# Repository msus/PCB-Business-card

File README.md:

# PCB Business Card with TicTacToe
#Main Points
- Designed around the Texas Instruments MSP430 series [g2553 16 bit MCU](https://www.ti.com/product/MSP430G2553).
- PCB schematics and board layout files for EAGLE are included.
- The PCB allows to play vs another human OR vs minimax algorithem.

#Image

#MCU LEDs pinout
MCU Pin | LED |MCU Pin | LED |MCU Pin | LED 
:-----:|:----:|:----:|:----:|:----:|:----:
P3.4  |  BLUE 2   |   P3.1  |  BLUE 1  |   P1.0  | BLUE 0
P2.3  |  RED  2   |   P3.0  |  RED  1   |   P1.1  |  RED  0
P2.4  |  BLUE 5   |   P2.0  |  BLUE 4  |   P1.2  |  BLUE 3
P2.5  |  RED  5   |   P2.1  |  RED  4   |   P1.3  |  RED  3
P3.5  |  BLUE 8   |   P2.2  |  BLUE 7  |   P1.4  |  BLUE 6
P3.6  |  RED  8   |   P3.2  |  RED  7   |   P1.5  |  RED  6

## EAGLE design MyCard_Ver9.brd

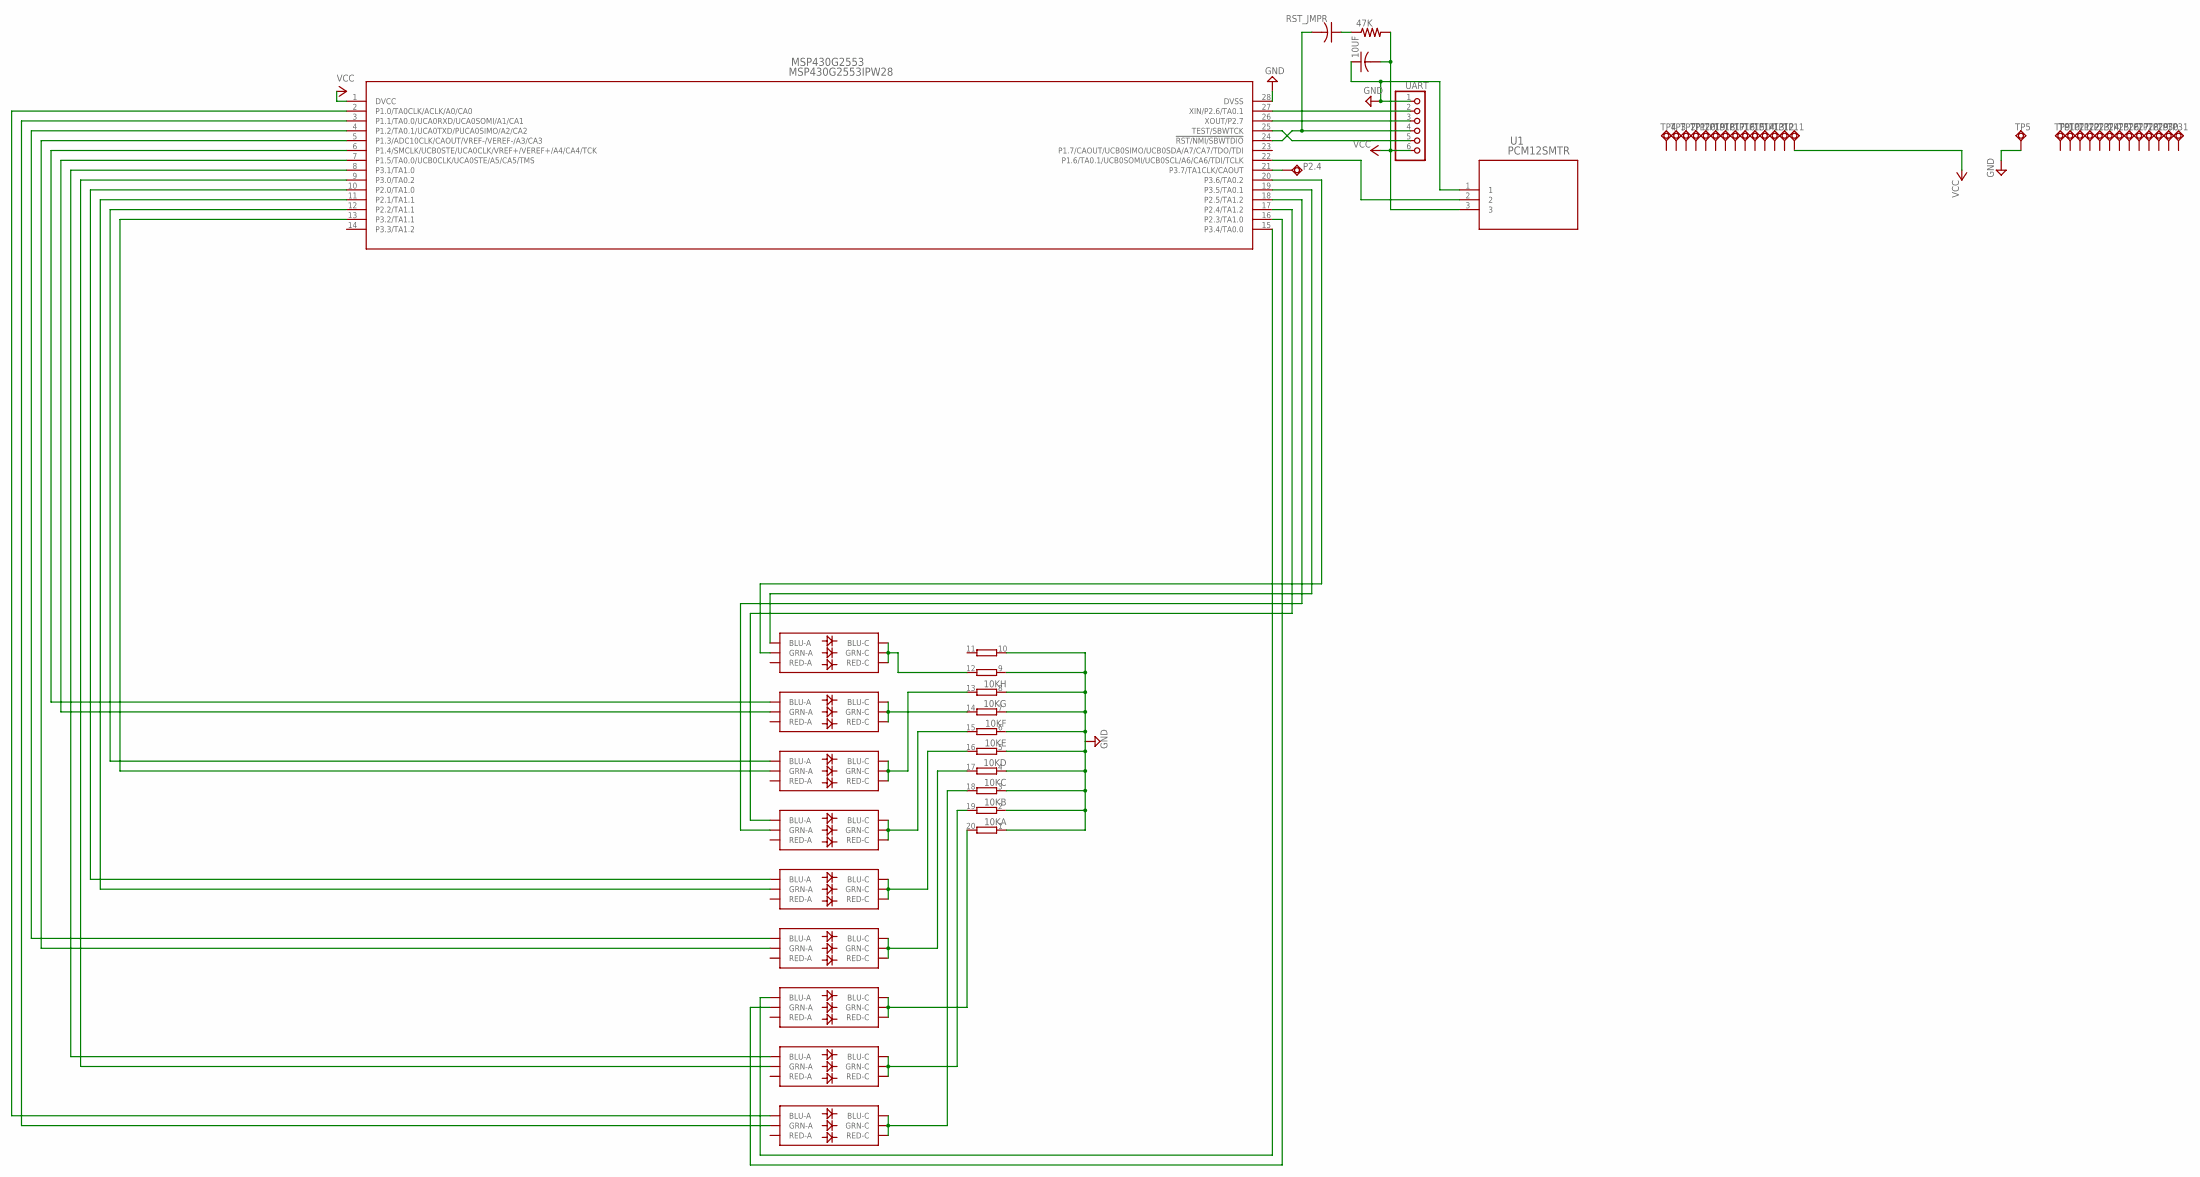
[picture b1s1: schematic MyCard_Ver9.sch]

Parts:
0, 1, 2, 3, 4, 5, 6, 7, 8: RGB; PLCC-6-LED
10K: 10R-NSOMC; SOMC20
10UF: C-USC0805; C0805
47K: R-US_R0805; R0805
MSP430G2553: MSP430G2553IPW28; PW28
P2.4: TPSQTP20R; TP20R
RST_JMPR: C-USC0805; C0805
TP1, TP2, TP3, TP4, TP5, TP9, TP10, TP11, TP12, TP13, TP14, TP15, TP16, TP17, TP18, TP19, TP20, TP21, TP22, TP23, TP24, TP25, TP26, TP27, TP28, TP29, TP30, TP31: TPSQTP20SQ; TP20SQ
U1: PCM12SMTR; PCM12SMTR_CNK
UART: PINHD-1X6B; 1X06-BIG

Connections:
GND: 10K.1, 10K.2 (1), 10K.3 (1), 10K.4 (1), 10K.5 (1), 10K.6 (1), 10K.7 (1), 10K.8 (1), 10K.9 (1), 10K.10 (1), 10UF.1, MSP430G2553.28 (DVSS), TP5.TP, U1.1, UART.1
unnamed: 1.CB (BLU-C), 1.CG (GRN-C), 1.CR (RED-C), 10K.19 (2)
unnamed: MSP430G2553.21 (P3.7/TA1CLK/CAOUT), P2.4.TP
unnamed: 8.CB (BLU-C), 8.CG (GRN-C), 8.CR (RED-C), 10K.12 (2)
unnamed: 0.CB (BLU-C), 0.CG (GRN-C), 0.CR (RED-C), 10K.18 (2)
unnamed: MSP430G2553.27 (XIN/P2.6/TA0.1), UART.2
unnamed: MSP430G2553.26 (XOUT/P2.7), UART.3
unnamed: 3.CB (BLU-C), 3.CG (GRN-C), 3.CR (RED-C), 10K.17 (2)
unnamed: 0.AB (BLU-A), MSP430G2553.2 (P1.0/TA0CLK/ACLK/A0/CA0)
unnamed: 0.AG (GRN-A), MSP430G2553.3 (P1.1/TA0.0/UCA0RXD/UCA0SOMI/A1/CA1)
unnamed: 3.AB (BLU-A), MSP430G2553.4 (P1.2/TA0.1/UCA0TXD/PUCA0SIMO/A2/CA2)
unnamed: 3.AG (GRN-A), MSP430G2553.5 (P1.3/ADC10CLK/CAOUT/VREF-/VEREF-/A3/CA3)
unnamed: 4.CB (BLU-C), 4.CG (GRN-C), 4.CR (RED-C), 10K.16 (2)
unnamed: 5.CB (BLU-C), 5.CG (GRN-C), 5.CR (RED-C), 10K.15 (2)
unnamed: 6.AB (BLU-A), MSP430G2553.6 (P1.4/SMCLK/UCB0STE/UCA0CLK/VREF+/VEREF+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)
unnamed: 6.AG (GRN-A), MSP430G2553.7 (P1.5/TA0.0/UCB0CLK/UCA0STE/A5/CA5/TMS)
unnamed: 1.AB (BLU-A), MSP430G2553.8 (P3.1/TA1.0)
unnamed: 1.AG (GRN-A), MSP430G2553.9 (P3.0/TA0.2)
unnamed: 6.CB (BLU-C), 6.CG (GRN-C), 6.CR (RED-C), 10K.14 (2)
unnamed: 4.AB (BLU-A), MSP430G2553.10 (P2.0/TA1.0)
unnamed: 7.CB (BLU-C), 7.CG (GRN-C), 7.CR (RED-C), 10K.13 (2)
unnamed: 4.AG (GRN-A), MSP430G2553.11 (P2.1/TA1.1)
unnamed: 7.AB (BLU-A), MSP430G2553.12 (P2.2/TA1.1)
unnamed: 7.AG (GRN-A), MSP430G2553.13 (P3.2/TA1.1)
unnamed: 47K.1, RST_JMPR.1
unnamed: 2.AB (BLU-A), MSP430G2553.15 (P3.4/TA0.0)
unnamed: 2.AG (GRN-A), MSP430G2553.16 (P2.3/TA1.0)
unnamed: 5.AB (BLU-A), MSP430G2553.17 (P2.4/TA1.2)
unnamed: 5.AG (GRN-A), MSP430G2553.18 (P2.5/TA1.2)
unnamed: 8.AB (BLU-A), MSP430G2553.19 (P3.5/TA0.1)
unnamed: 8.AG (GRN-A), MSP430G2553.20 (P3.6/TA0.2)
unnamed: MSP430G2553.22 (P1.6/TA0.1/UCB0SOMI/UCB0SCL/A6/CA6/TDI/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), U1.2
unnamed: 2.CB (BLU-C), 2.CG (GRN-C), 2.CR (RED-C), 10K.20 (2)
RST: MSP430G2553.24 (!RST/NMI/SBWTDIO), RST_JMPR.2, UART.4
TEST: MSP430G2553.25 (TEST/SBWTCK), UART.5
VCC: 10UF.2, 47K.2, MSP430G2553.1 (DVCC), TP11.TP, U1.3, UART.6

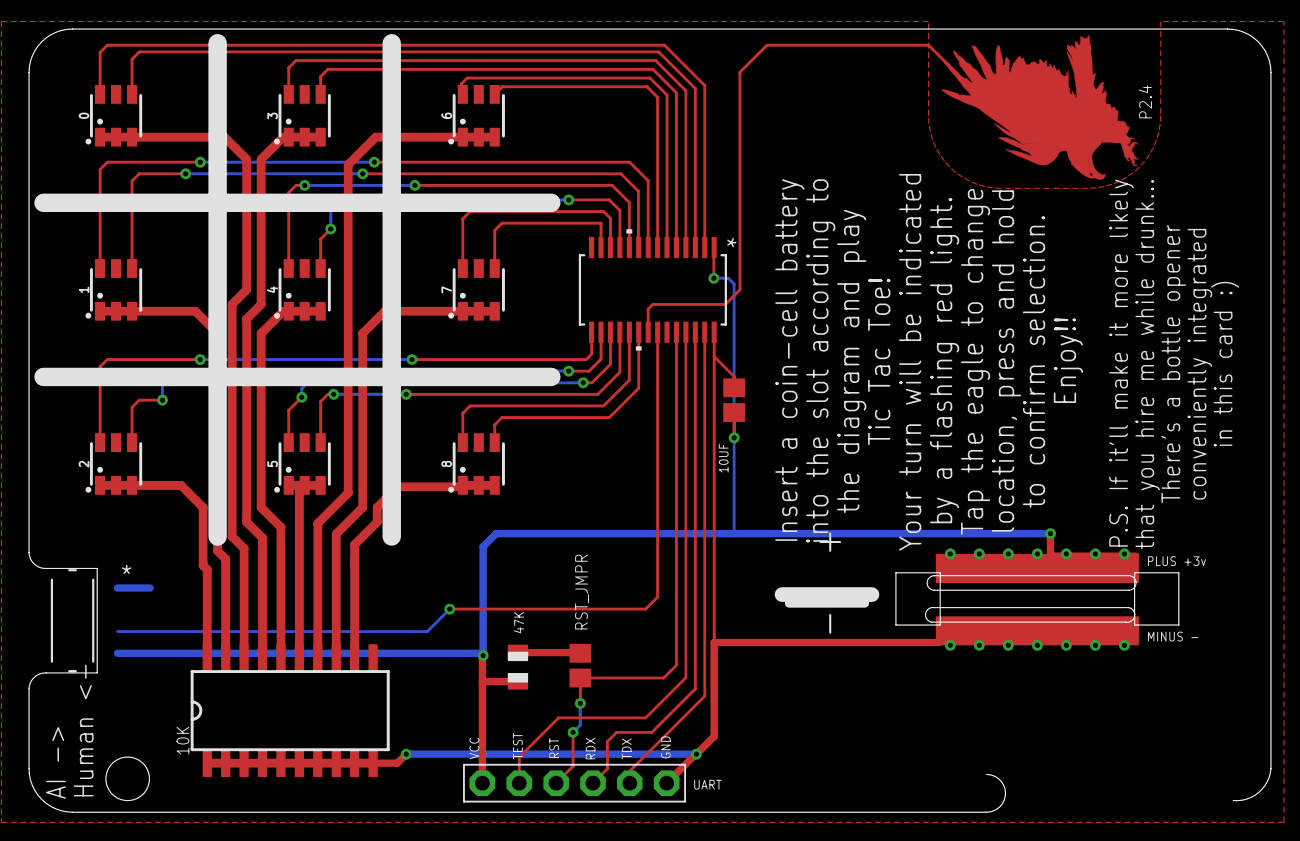
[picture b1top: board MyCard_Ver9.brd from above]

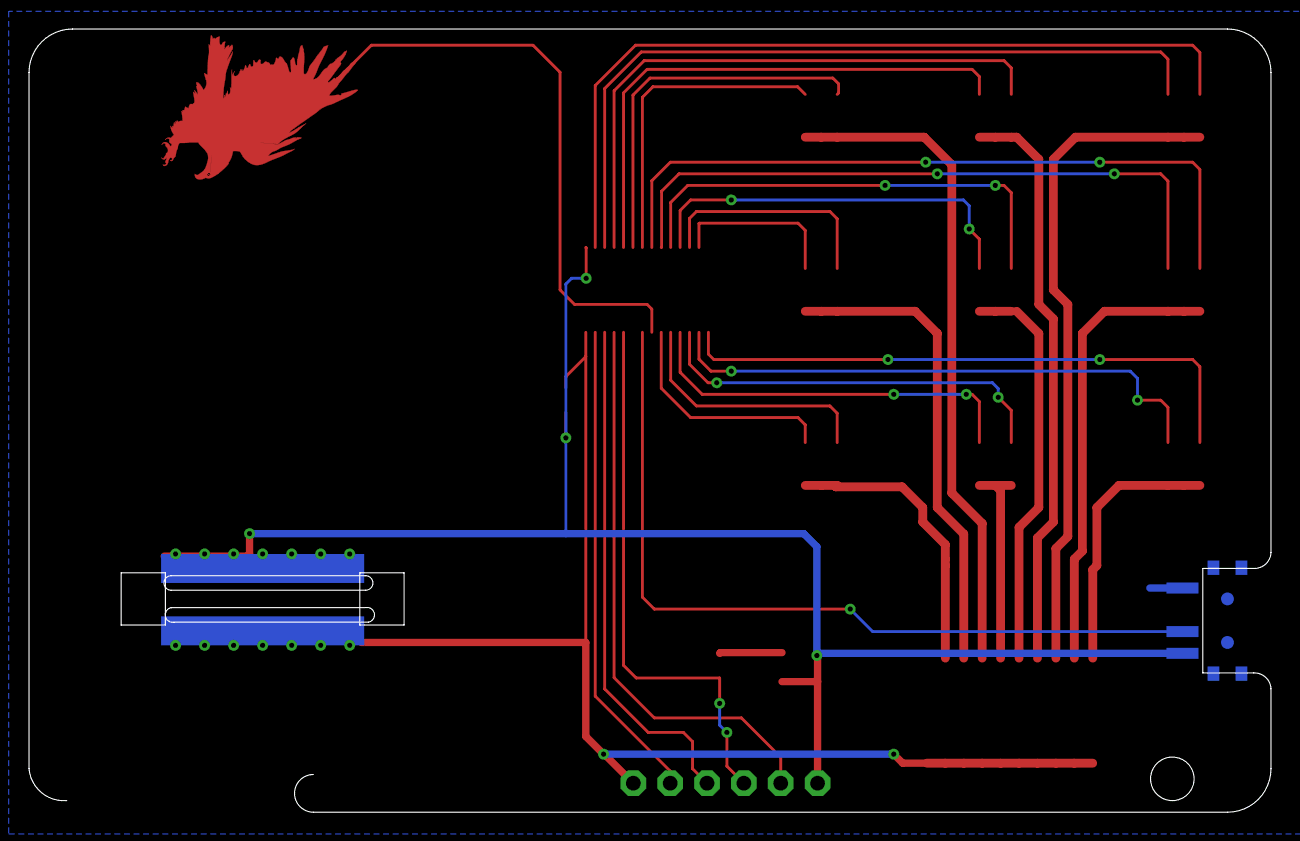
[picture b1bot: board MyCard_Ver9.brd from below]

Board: 2 copper layers, 85.6 x 54.0 mm, 46 parts (14 on the bottom side), 36 nets.

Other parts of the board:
U$2: EAGLE-TOP-10MM

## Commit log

2023-05-16 fix readme

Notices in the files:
parts and their libraries:
SparkFun-LED: Licensing: Creative Commons ShareAlike 4.0 International - https://creativecommons.org/licenses/by-sa/4.0
COPYRIGHT: Copyright (C) 2023 Ultra Librarian. All rights reserved.
